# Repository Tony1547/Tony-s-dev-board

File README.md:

# Tony's-dev-board
Following the dev-board tutorial & adding an awesome case (that can be put on a keychain)

CAD: https://cad.onshape.com/documents/c5034cab5a6af16967bc6f77/w/0904c445d2f2abc194a185dd/e/55b6160e95263006e3b240b2 (also in the files)

BOM: https://docs.google.com/spreadsheets/d/1fPphZmWIDkRLiHGIMIhjy6UCU6EgHhpaO0yYP-10utQ/edit?gid=1931436732#gid=1931436732 (also in the files)

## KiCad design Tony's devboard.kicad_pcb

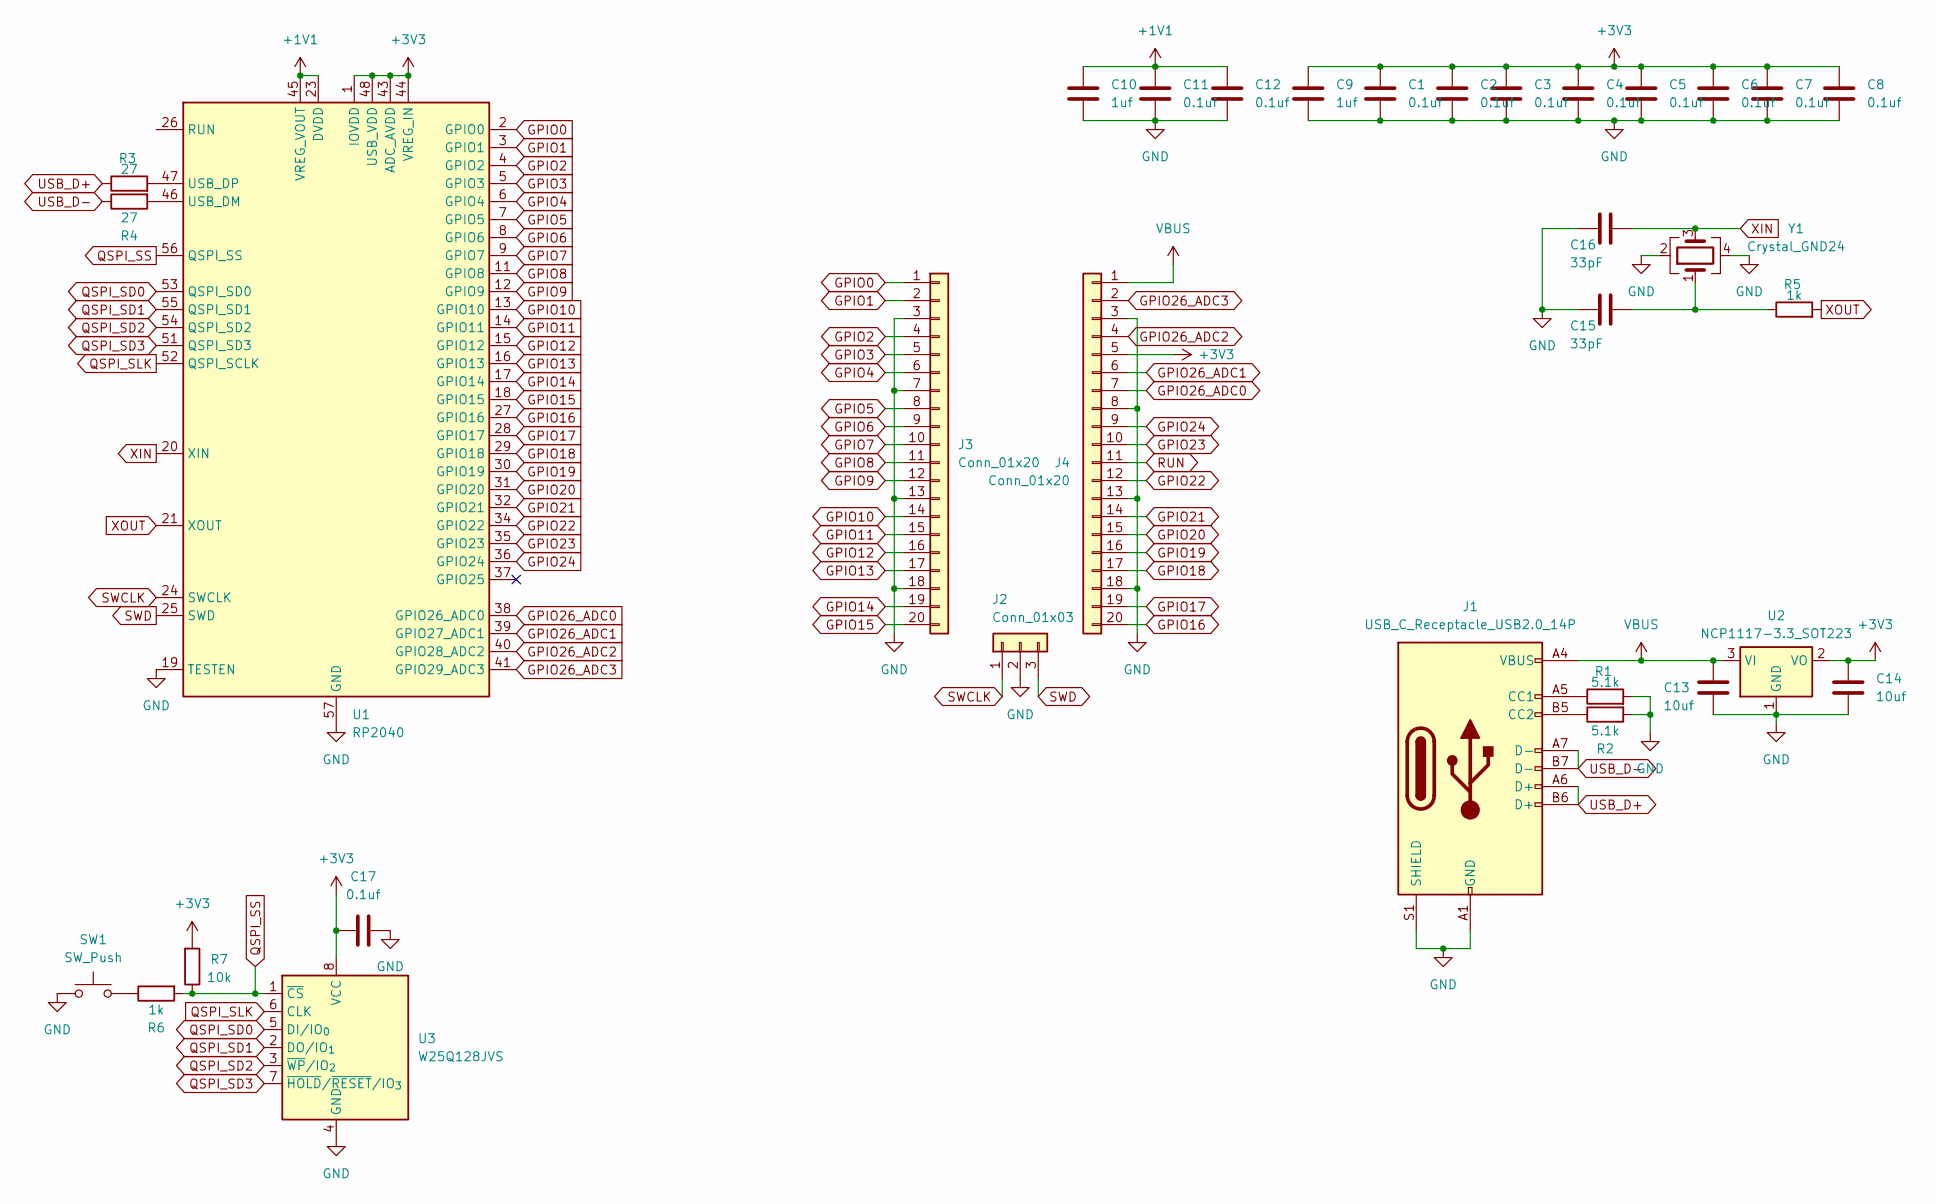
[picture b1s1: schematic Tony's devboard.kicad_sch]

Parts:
C1, C2, C3, C4, C5, C6, C7, C8, C11, C12, C17: 0.1uf; C_0201_0603Metric_Pad0.64x0.40mm_HandSolder
C9, C10: 1uf; C_0201_0603Metric_Pad0.64x0.40mm_HandSolder
C13, C14: 10uf; C_0201_0603Metric_Pad0.64x0.40mm_HandSolder
C15, C16: 33pF; C_0201_0603Metric_Pad0.64x0.40mm_HandSolder
J1: USB_C_Receptacle_USB2.0_14P; USB_C_Receptacle_GCT_USB4105-xx-A_16P_TopMnt_Horizontal
J2: Conn_01x03; PinHeader_1x03_P2.54mm_Vertical; Part Number 1-0301FBV0T
J3, J4: Conn_01x20; Molex_SL_171971-0020_1x20_P2.54mm_Vertical
R1, R2: 5.1k; R_0201_0603Metric_Pad0.64x0.40mm_HandSolder
R3, R4: 27; R_0201_0603Metric_Pad0.64x0.40mm_HandSolder
R5, R6: 1k; R_0201_0603Metric_Pad0.64x0.40mm_HandSolder
R7: 10k; R_0201_0603Metric_Pad0.64x0.40mm_HandSolder
SW1: SW_Push; SW_PUSH_1P1T_6x3.5mm_H5.0_APEM_MJTP1250
U1: RP2040; QFN-56-1EP_7x7mm_P0.4mm_EP3.2x3.2mm
U2: NCP1117-3.3_SOT223; SOT-223-3_TabPin2
U3: W25Q128JVS; SOIC-8_5.3x5.3mm_P1.27mm
Y1: Crystal_GND24; Crystal_SMD_0603-4Pin_6.0x3.5mm_HandSoldering

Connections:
+1V1: C10.1, C11.1, C12.1, U1.23 (DVDD), U1.45 (VREG_VOUT), U1.50 (DVDD)
+3V3: C1.1, C2.1, C3.1, C4.1, C5.1, C6.1, C7.1, C8.1, C9.1, C14.1, C17.1, J4.5, R7.2, U1.1 (IOVDD), U1.10 (IOVDD), U1.22 (IOVDD), U1.33 (IOVDD), U1.42 (IOVDD), U1.43 (ADC_AVDD), U1.44 (VREG_IN), U1.48 (USB_VDD), U1.49 (IOVDD), U2.2 (VO), U3.8 (VCC)
GND: C1.2, C2.2, C3.2, C4.2, C5.2, C6.2, C7.2, C8.2, C9.2, C10.2, C11.2, C12.2, C13.2, C14.2, C15.1, C16.1, C17.2, J1.A1 (GND), J1.A12 (GND), J1.B1 (GND), J1.B12 (GND), J1.S1 (SHIELD), J2.2, J3.3, J3.7, J3.13, J3.18, J4.3, J4.8, J4.13, J4.18, R1.2, R2.2, SW1.1, U1.19 (TESTEN), U1.57 (GND), U2.1 (GND), U3.4 (GND), Y1.2, Y1.4
GPIO0: J3.1, U1.2 (GPIO0)
GPIO1: J3.2, U1.3 (GPIO1)
GPIO2: J3.4, U1.4 (GPIO2)
GPIO3: J3.5, U1.5 (GPIO3)
GPIO4: J3.6, U1.6 (GPIO4)
GPIO5: J3.8, U1.7 (GPIO5)
GPIO6: J3.9, U1.8 (GPIO6)
GPIO7: J3.10, U1.9 (GPIO7)
GPIO8: J3.11, U1.11 (GPIO8)
GPIO9: J3.12, U1.12 (GPIO9)
GPIO10: J3.14, U1.13 (GPIO10)
GPIO11: J3.15, U1.14 (GPIO11)
GPIO12: J3.16, U1.15 (GPIO12)
GPIO13: J3.17, U1.16 (GPIO13)
GPIO14: J3.19, U1.17 (GPIO14)
GPIO15: J3.20, U1.18 (GPIO15)
GPIO16: J4.20, U1.27 (GPIO16)
GPIO17: J4.19, U1.28 (GPIO17)
GPIO18: J4.17, U1.29 (GPIO18)
GPIO19: J4.16, U1.30 (GPIO19)
GPIO20: J4.15, U1.31 (GPIO20)
GPIO21: J4.14, U1.32 (GPIO21)
GPIO22: J4.12, U1.34 (GPIO22)
GPIO23: J4.10, U1.35 (GPIO23)
GPIO24: J4.9, U1.36 (GPIO24)
GPIO26_ADC0: J4.7, U1.38 (GPIO26_ADC0)
GPIO26_ADC1: J4.6, U1.39 (GPIO27_ADC1)
GPIO26_ADC2: J4.4, U1.40 (GPIO28_ADC2)
GPIO26_ADC3: J4.2, U1.41 (GPIO29_ADC3)
unnamed: C15.2, R5.1, Y1.1
unnamed: J1.A5 (CC1), R1.1
unnamed: J1.B5 (CC2), R2.1
unnamed: R6.1, SW1.2
unnamed: R4.2, U1.46 (USB_DM)
unnamed: R3.2, U1.47 (USB_DP)
QSPI_SD0: U1.53 (QSPI_SD0), U3.5 (DI/IO_{0})
QSPI_SD1: U1.55 (QSPI_SD1), U3.2 (DO/IO_{1})
QSPI_SD2: U1.54 (QSPI_SD2), U3.3 (~WP/IO_{2})
QSPI_SD3: U1.51 (QSPI_SD3), U3.7 (~HOLD/~RESET/IO_{3})
QSPI_SLK: U1.52 (QSPI_SCLK), U3.6 (CLK)
QSPI_SS: R6.2, R7.1, U1.56 (QSPI_SS), U3.1 (~CS)
RUN: J4.11
SWCLK: J2.1, U1.24 (SWCLK)
SWD: J2.3, U1.25 (SWD)
USB_D+: J1.A6 (D+), J1.B6 (D+), R3.1
USB_D-: J1.A7 (D-), J1.B7 (D-), R4.1
VBUS: C13.1, J1.A4 (VBUS), J1.A9 (VBUS), J1.B4 (VBUS), J1.B9 (VBUS), J4.1, U2.3 (VI)
XIN: C16.2, U1.20 (XIN), Y1.3
XOUT: R5.2, U1.21 (XOUT)

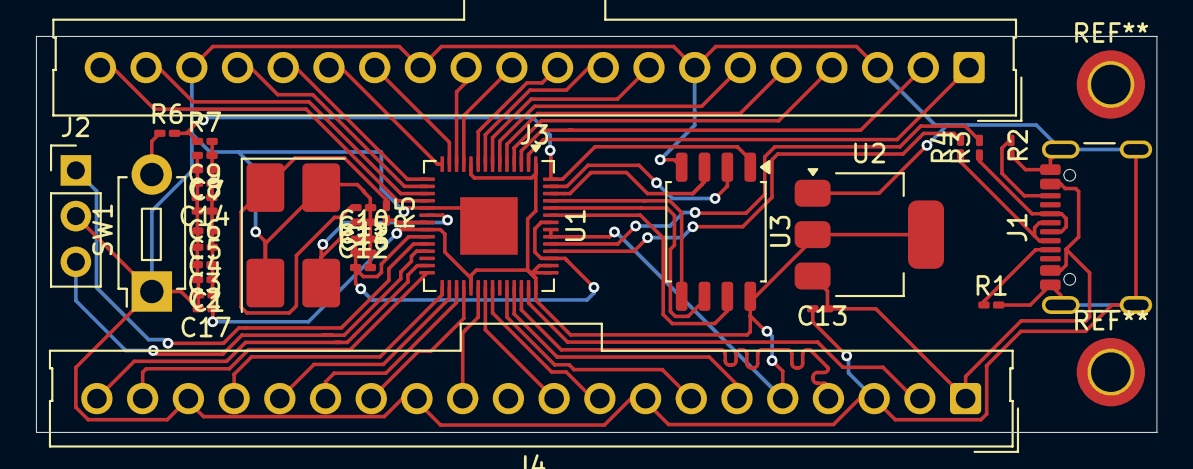
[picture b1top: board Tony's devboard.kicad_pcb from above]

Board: 2 copper layers, 62.2 x 22.0 mm, 33 parts (0 on the bottom side), 51 nets.

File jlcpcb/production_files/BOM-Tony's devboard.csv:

Comment,Designator,Footprint,LCSC,Quantity
1uf,C10,C_0201_0603Metric_Pad0.64x0.40mm_HandSolder,,1
1uf,C9,C_0201_0603Metric_Pad0.64x0.40mm_HandSolder,,1
Conn_01x20,J4,Molex_SL_171971-0020_1x20_P2.54mm_Vertical,,1
10uf,C14,C_0201_0603Metric_Pad0.64x0.40mm_HandSolder,,1
33pF,C15,C_0201_0603Metric_Pad0.64x0.40mm_HandSolder,,1
NCP1117-3.3_SOT223,U2,SOT-223-3_TabPin2,,1
0.1uf,C12,C_0201_0603Metric_Pad0.64x0.40mm_HandSolder,,1
Conn_01x20,J3,Molex_SL_171971-0020_1x20_P2.54mm_Vertical,,1
27,R3,R_0201_0603Metric_Pad0.64x0.40mm_HandSolder,,1
10uf,C13,C_0201_0603Metric_Pad0.64x0.40mm_HandSolder,,1
0.1uf,C3,C_0201_0603Metric_Pad0.64x0.40mm_HandSolder,,1
USB_C_Receptacle_USB2.0_14P,J1,USB_C_Receptacle_GCT_USB4105-xx-A_16P_TopMnt_Horizontal,,1
10k,R7,R_0201_0603Metric_Pad0.64x0.40mm_HandSolder,,1
Conn_01x03,J2,PinHeader_1x03_P2.54mm_Vertical,,1
1k,R6,R_0201_0603Metric_Pad0.64x0.40mm_HandSolder,,1
0.1uf,C4,C_0201_0603Metric_Pad0.64x0.40mm_HandSolder,,1
SW_Push,SW1,SW_PUSH_1P1T_6x3.5mm_H5.0_APEM_MJTP1250,,1
0.1uf,C8,C_0201_0603Metric_Pad0.64x0.40mm_HandSolder,,1
0.1uf,C5,C_0201_0603Metric_Pad0.64x0.40mm_HandSolder,,1
RP2040,U1,QFN-56-1EP_7x7mm_P0.4mm_EP3.2x3.2mm,,1
5.1k,R2,R_0201_0603Metric_Pad0.64x0.40mm_HandSolder,,1
Crystal_GND24,Y1,Crystal_SMD_0603-4Pin_6.0x3.5mm_HandSoldering,,1
0.1uf,C1,C_0201_0603Metric_Pad0.64x0.40mm_HandSolder,,1
0.1uf,C6,C_0201_0603Metric_Pad0.64x0.40mm_HandSolder,,1
0.1uf,C17,C_0201_0603Metric_Pad0.64x0.40mm_HandSolder,,1
5.1k,R1,R_0201_0603Metric_Pad0.64x0.40mm_HandSolder,,1
33pF,C16,C_0201_0603Metric_Pad0.64x0.40mm_HandSolder,,1
0.1uf,C2,C_0201_0603Metric_Pad0.64x0.40mm_HandSolder,,1
0.1uf,C11,C_0201_0603Metric_Pad0.64x0.40mm_HandSolder,,1
0.1uf,C7,C_0201_0603Metric_Pad0.64x0.40mm_HandSolder,,1
1k,R5,R_0201_0603Metric_Pad0.64x0.40mm_HandSolder,,1
W25Q128JVS,U3,SOIC-8_5.3x5.3mm_P1.27mm,,1
27,R4,R_0201_0603Metric_Pad0.64x0.40mm_HandSolder,,1

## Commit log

2025-11-30 Extra fab files
2025-11-30 Upload files
2025-11-30 renamed file
2025-12-02 move .csv
2025-12-02 BOM added to front
